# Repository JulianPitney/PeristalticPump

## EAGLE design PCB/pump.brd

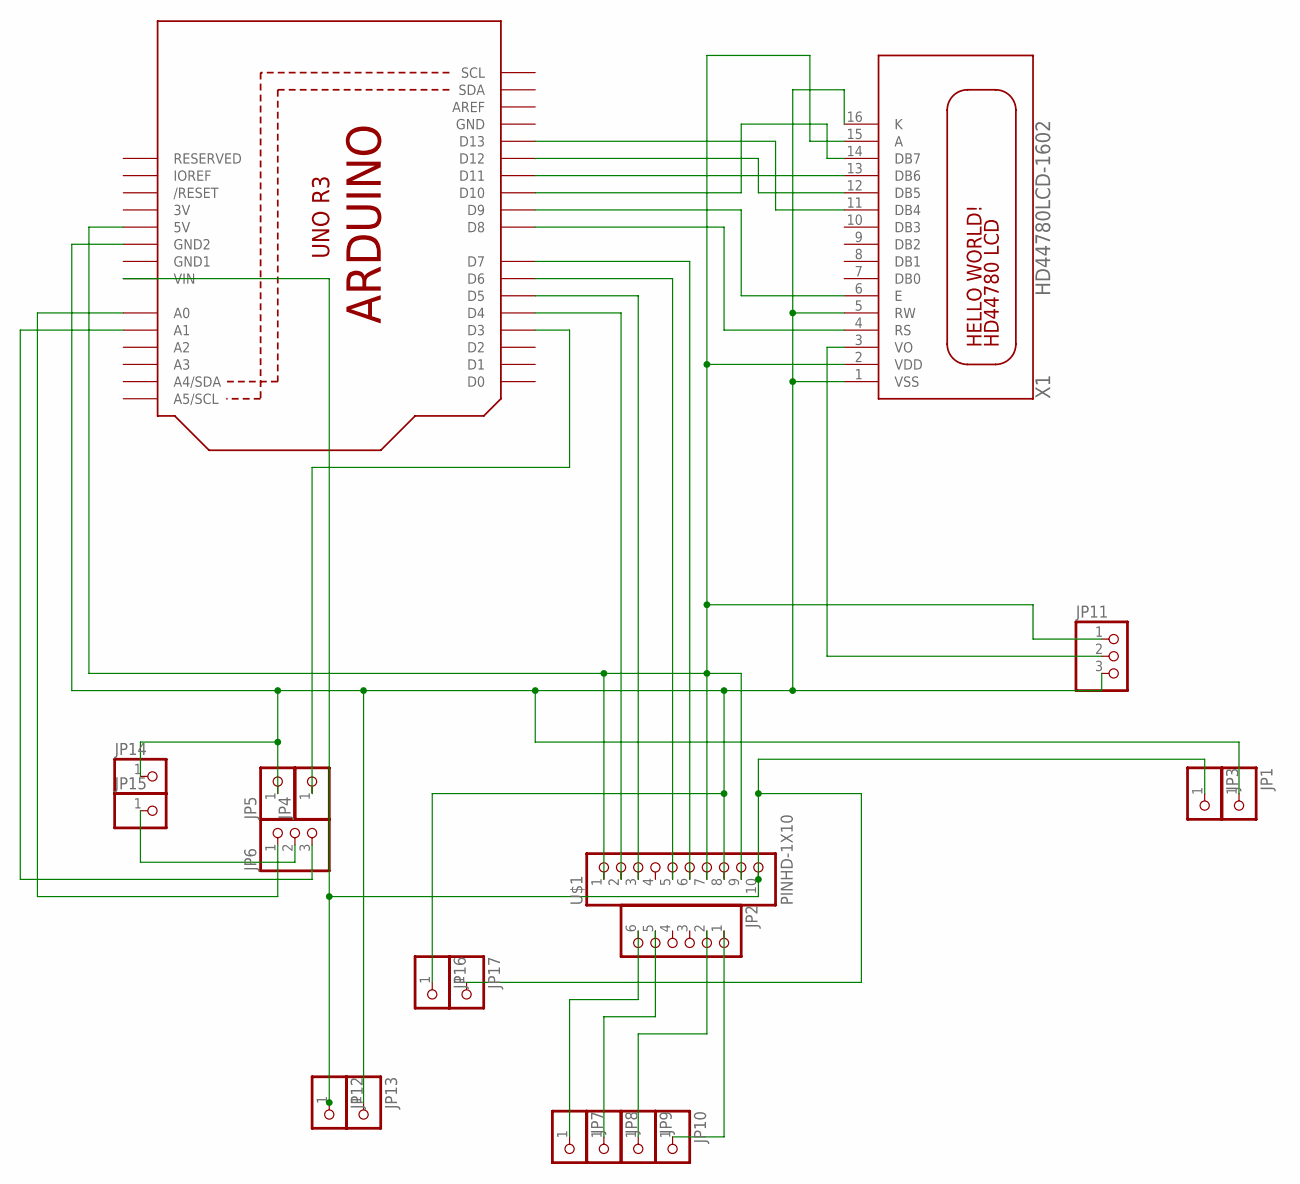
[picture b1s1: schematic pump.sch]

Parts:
JP1, JP3, JP4, JP5: PINHD-1X1CB; 1X01-CLEANBIG
JP2: PINHD-1X6CB; 1X06-CLEANBIG
JP6, JP11: PINHD-1X3; 1X03
JP7, JP8, JP9, JP10, JP12, JP13, JP14, JP15, JP16, JP17: PINHD-1X1; 1X01
U1: ARDUINOR3-BPLACE
U$1: PINHD-1X10; 1X10-BIG
X1: HD44780LCD-1602; LCD1602

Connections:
3V: U1.3V
GND: U1.GND
GND1: U1.GND1
unnamed: JP6.2, JP15.1
unnamed: JP6.1, U1.A0
unnamed: JP6.3, U1.A1
unnamed: JP3.1, JP12.1, JP17.1, U1.VIN, U$1.10
unnamed: JP4.1, U1.D3
unnamed: JP11.2, X1.3 (VO)
unnamed: U1.D13, X1.11 (DB4)
unnamed: U1.D12, X1.12 (DB5)
unnamed: U1.D11, X1.13 (DB6)
unnamed: U1.D10, X1.14 (DB7)
unnamed: U1.D9, X1.6 (E)
unnamed: U1.D8, X1.4 (RS)
unnamed: U1.D7, U$1.6
unnamed: U1.D6, U$1.5
unnamed: U1.D5, U$1.3
unnamed: U1.D4, U$1.2
unnamed: JP2.6, JP7.1
unnamed: JP2.5, JP8.1
unnamed: JP2.2, JP9.1
unnamed: JP2.1, JP10.1
VDD: JP11.1, U1.5V, U$1.1, U$1.7, U$1.9, X1.2 (VDD), X1.15 (A)
VSS: JP1.1, JP5.1, JP11.3, JP13.1, JP14.1, JP16.1, U1.GND2, U$1.8, X1.1 (VSS), X1.5 (RW), X1.16 (K)

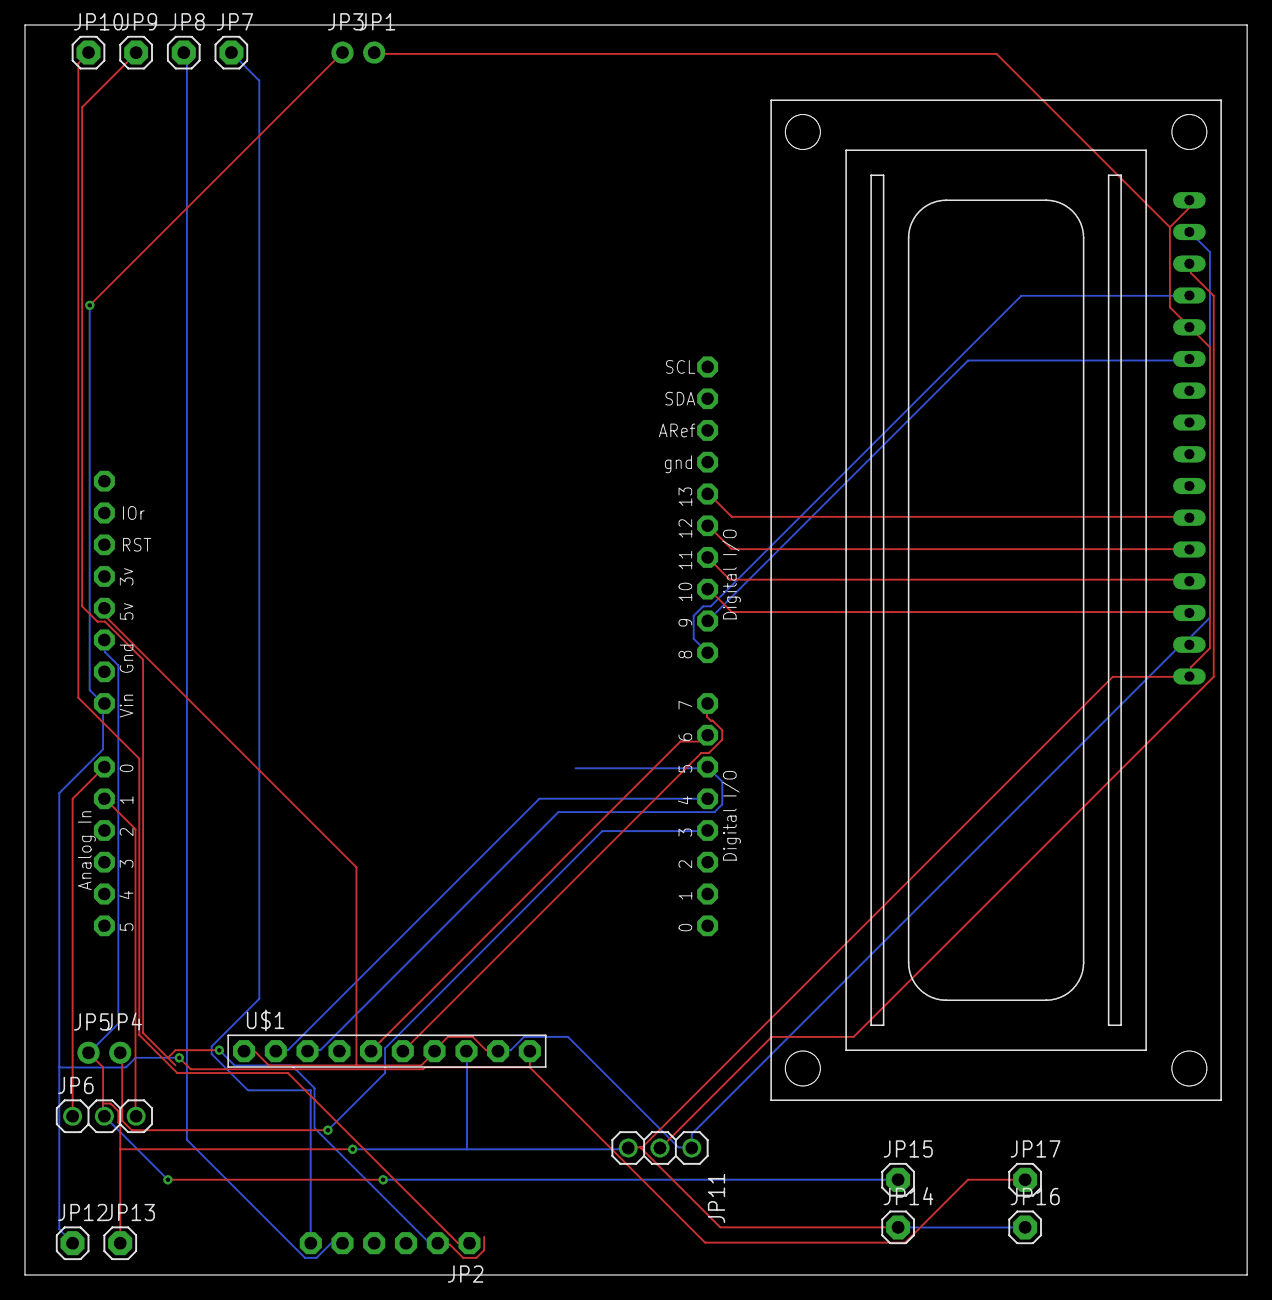
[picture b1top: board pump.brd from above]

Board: 2 copper layers, 97.8 x 100.0 mm, 20 parts (0 on the bottom side), 22 nets.

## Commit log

2019-06-27 Added PCB files
2019-06-27 Updated wiring diagram
2019-06-28 Finished PCB
2019-07-29 Fixed driver spacing on PCB and rerouted traces
2020-01-16 Adding source code
2020-01-16 Added libraries for storage and added encoder click pump reset
